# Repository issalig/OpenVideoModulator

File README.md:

# rgbs
rgbs is an Open Hardware adapter that converts an RGB video signal to Composite and S-Video.

This is a fork of https://github.com/SukkoPera/OpenVideoModulator with independent RCA and SVideo connector, pin header for output signals and 5V DC jack.

There are also designs for breakout boards that could be inside CPC 464 and 6128 and it would be plugged on the space left in the left side (viewed from rear) of the expansion port. 
It requires to open the computer and solder wires from RGBS 5V GND to the breakout board, then it could be connected with right angle pinheaders to the main board saving the additional 5V line.

I have NOT physically checked this. So, trying is up to you.

## Summary
This project is an Open Hardware implementation of [a small circuit found on the Amstrad CPC Wiki](http://www.cpcwiki.eu/index.php/RGB_SVideo) that is able to produce a composite video signal from separate red, green and blue color component signals (plus sync). Since it uses the AD724 encoder, it is also able to produce an S-Video (Y/C) signal and it supports both the PAL and NTSC standards.

## Assembly and Usage

The crystal frequency depends on your choice: use 4.433619 MHz for PAL or 3.579545 MHz for NTSC.

Solder the AD724 chip first, then all surface-mount components. Finally complete the board with the through-hole connectors and crystal.

One of C6 and C7 should be enough. I use a 100uF on C6 but that is probably overkill. Play with them if your output video signal is unstable.

Usage should be straightforward: just provide power (make sure to match the polarity!) and video signals to the board, then get your output from the other side. Note that the *sync* input requires a *composite sync* signal.

## Problems and troubleshooting

If you get BW image check AD724 soldering.

In case of noise, check or change capacitors.

## Known issues

Quality is not the best. On my CPC I get black areas on the right side of characters.
If you know how to solve just tell it and we will improve the design.

## License
 Do whatever you want with it but give me credit.
 
## Thanks
- CPC Wiki for the original circuit.
- SukkoPera for original board

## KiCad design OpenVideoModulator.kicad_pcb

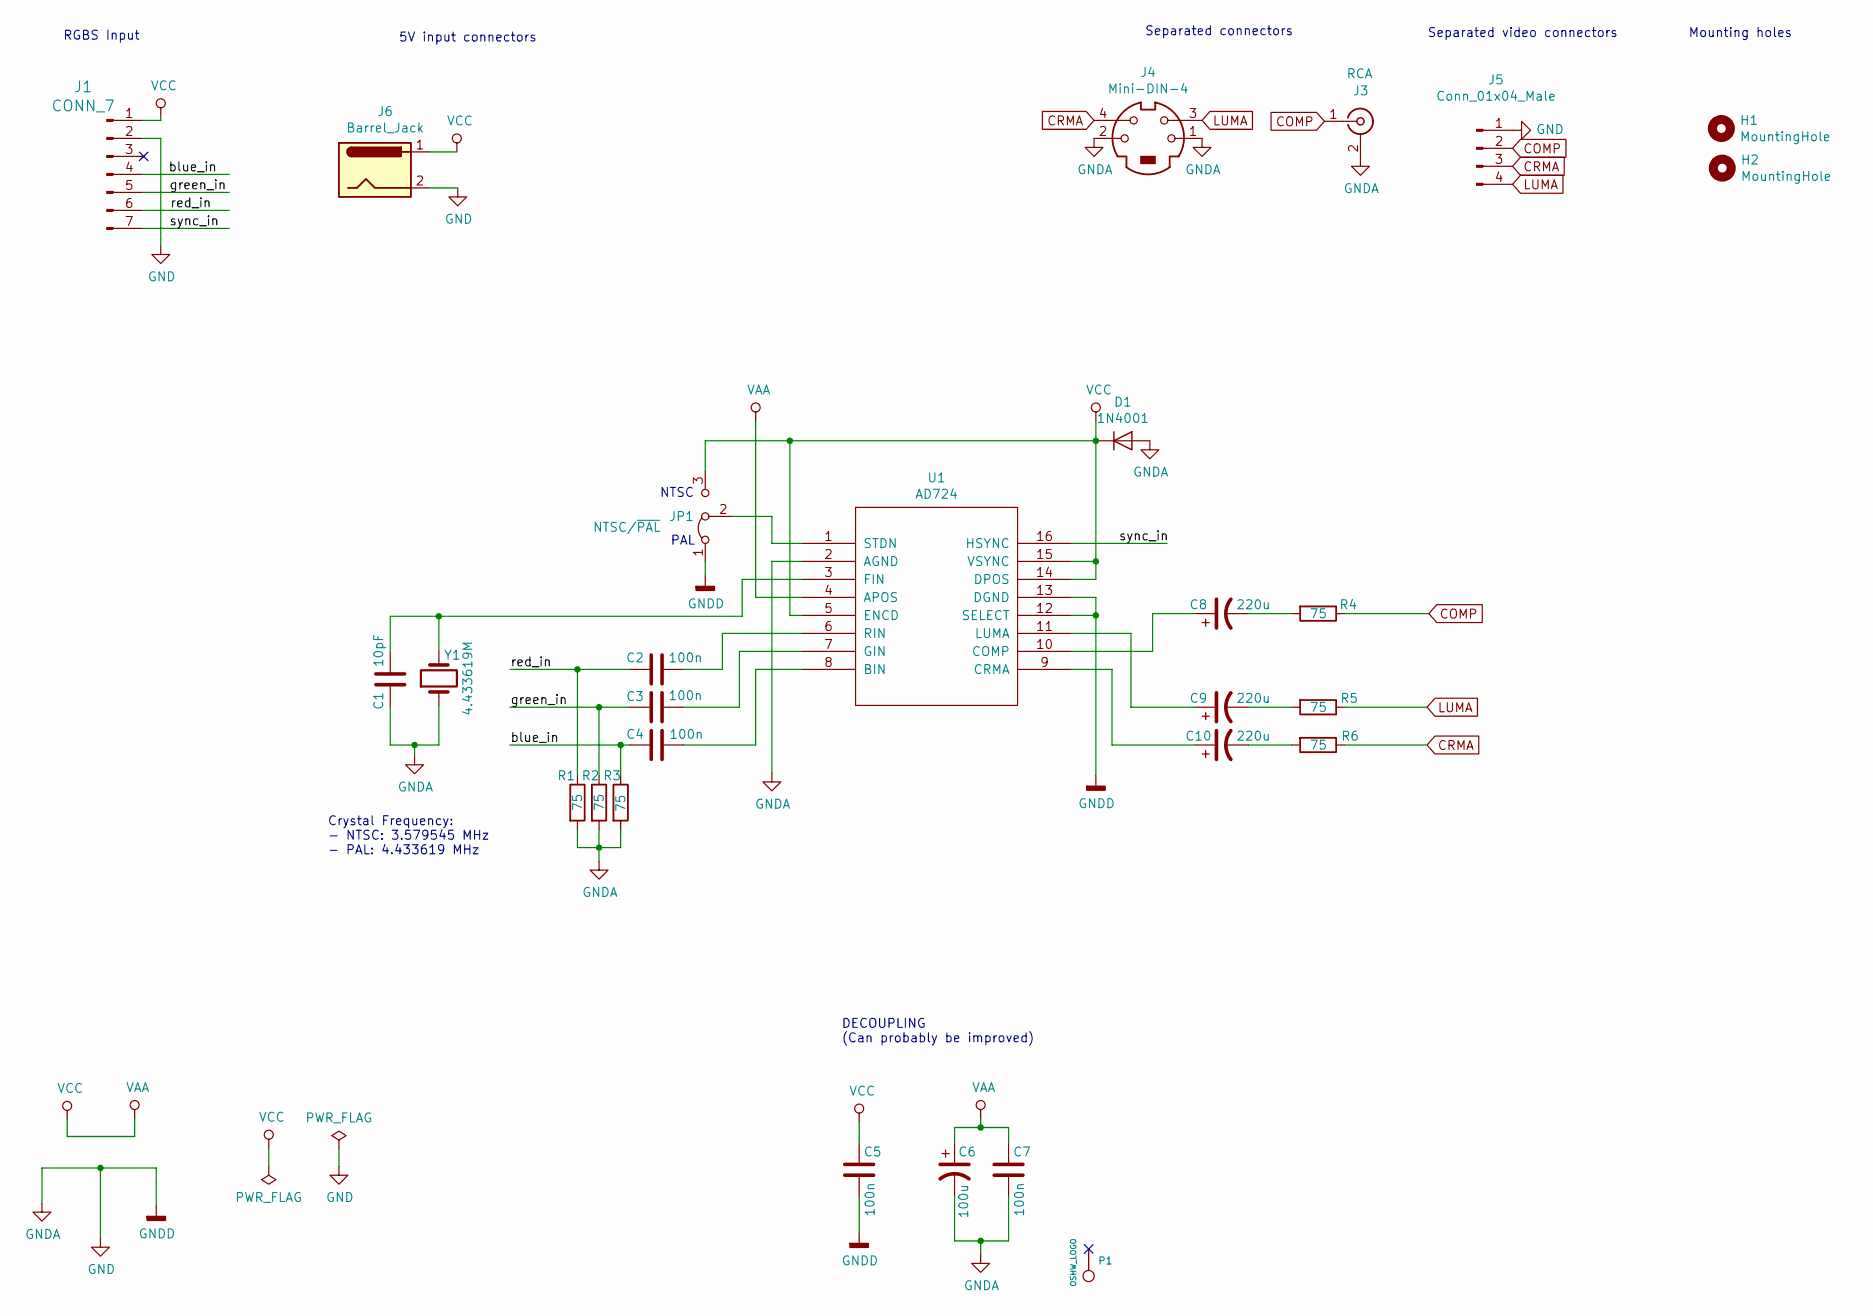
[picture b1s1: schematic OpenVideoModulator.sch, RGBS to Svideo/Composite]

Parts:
C1: 10pF; C_0805_2012Metric_Pad1.15x1.40mm_HandSolder
C2, C3, C4, C5, C7: 100n; C_0805_2012Metric_Pad1.15x1.40mm_HandSolder
C6: 100u; CP_Radial_D5.0mm_P2.00mm
C8, C9, C10: 220u; CP_Radial_D5.0mm_P2.00mm
D1: 1N4001; D_SMA
H1, H2: MountingHole; MountingHole_2.2mm_M2_ISO7380_Pad
J1: CONN_7; PinHeader_1x07_P2.54mm_Vertical
J3: RCA; CUI_RCJ-044
J4: Mini-DIN-4; CUI_MD-40S_1234
J5: Conn_01x04_Male; PinHeader_1x04_P2.54mm_Vertical
J6: Barrel_Jack; BarrelJack_Horizontal
JP1: NTSC/~PAL; PinHeader_1x03_P2.54mm_Vertical
P1: OSHW_LOGO; OSHW-Logo2_7.3x6mm_Copper
R1, R2, R3, R4, R5, R6: 75; R_0805_2012Metric_Pad1.15x1.40mm_HandSolder
U1: AD724; SOIC-16W_7.5x10.3mm_P1.27mm
Y1: 4.433619M; Crystal_HC49-4H_Vertical

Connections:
/blue_in: C4.2, J1.4, R3.1
/green_in: C3.2, J1.5, R2.1
/red_in: C2.2, J1.6, R1.1
/sync_in: J1.7, U1.16 (HSYNC)
COMP: J3.1 (In), J5.2, R4.1
CRMA: J4.4, J5.3, R6.1
GND: C1.2, C5.1, C6.2, C7.1, D1.2 (A), J1.2, J3.2 (Ext), J4.1, J4.2, J5.1, J6.2, JP1.1 (A), R1.2, R2.2, R3.2, U1.2 (AGND), U1.12 (SELECT), U1.13 (DGND), Y1.1
LUMA: J4.3, J5.4, R5.1
unnamed: C1.1, U1.3 (FIN), Y1.2
unnamed: C2.1, U1.6 (RIN)
unnamed: C3.1, U1.7 (GIN)
unnamed: C4.1, U1.8 (BIN)
unnamed: C8.1, U1.10 (COMP)
unnamed: C8.2, R4.2
unnamed: C9.1, U1.11 (LUMA)
unnamed: C9.2, R5.2
unnamed: C10.1, U1.9 (CRMA)
unnamed: C10.2, R6.2
unnamed: JP1.2 (C), U1.1 (STDN)
VAA: C5.2, C6.1, C7.2, D1.1 (K), J1.1, J6.1, JP1.3 (B), U1.4 (APOS), U1.5 (ENCD), U1.14 (DPOS), U1.15 (VSYNC)

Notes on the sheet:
PAL
NTSC
Crystal Frequency: - NTSC: 3.579545 MHz - PAL: 4.433619 MHz
Separated connectors
DECOUPLING (Can probably be improved)
RGBS Input
5V input connectors
Mounting holes
Separated video connectors

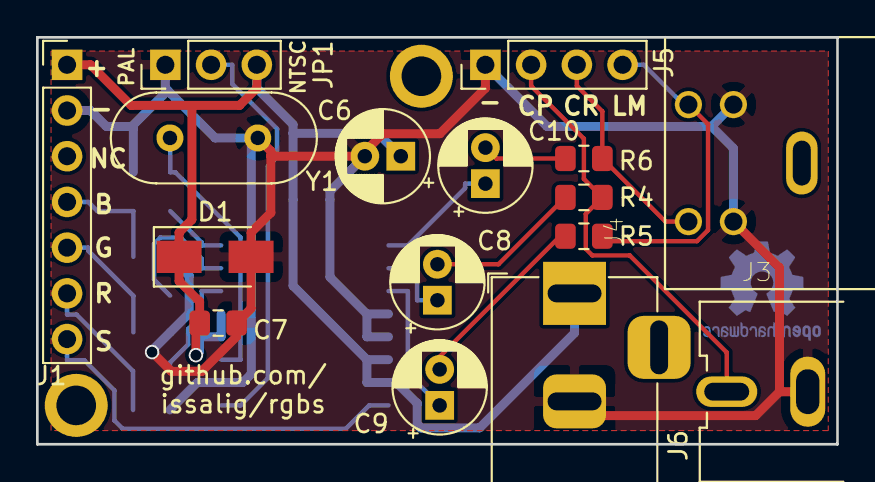
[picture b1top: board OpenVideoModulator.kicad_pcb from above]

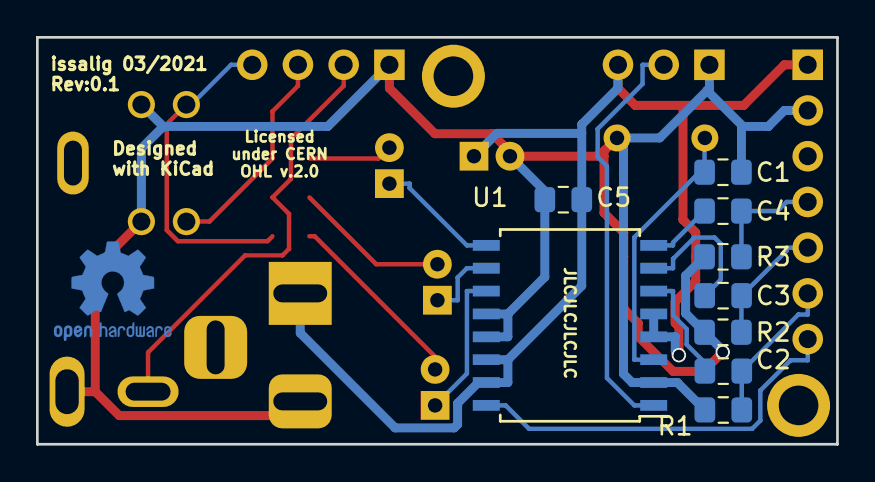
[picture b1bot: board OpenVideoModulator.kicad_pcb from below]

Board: 2 copper layers, 44.5 x 22.6 mm, 28 parts (10 on the bottom side), 20 nets.

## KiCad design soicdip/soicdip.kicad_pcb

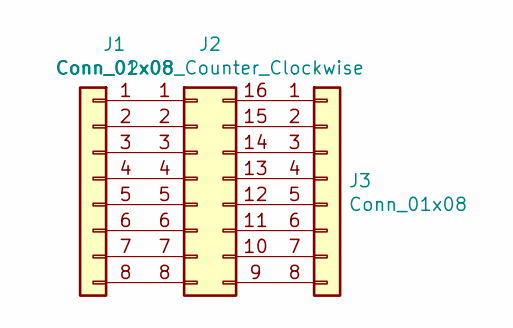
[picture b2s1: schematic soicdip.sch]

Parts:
J1, J3: Conn_01x08; PinHeader_1x08_P2.54mm_Vertical
J2: Conn_02x08_Counter_Clockwise; SOIC-16

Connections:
unnamed: J1.1, J2.1
unnamed: J1.2, J2.2
unnamed: J1.3, J2.3
unnamed: J1.4, J2.4
unnamed: J1.5, J2.5
unnamed: J1.6, J2.6
unnamed: J1.7, J2.7
unnamed: J1.8, J2.8
unnamed: J2.9, J3.8
unnamed: J2.10, J3.7
unnamed: J2.11, J3.6
unnamed: J2.12, J3.5
unnamed: J2.13, J3.4
unnamed: J2.14, J3.3
unnamed: J2.15, J3.2
unnamed: J2.16, J3.1

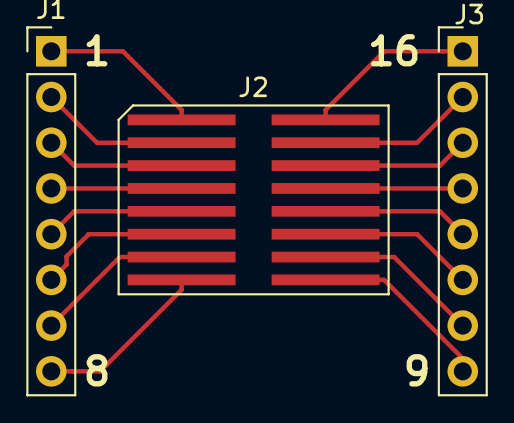
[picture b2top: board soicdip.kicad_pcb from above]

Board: 2 copper layers, 3 parts (0 on the bottom side), 16 nets.

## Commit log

2021-03-07 1st version
2021-03-07 readme
2021-03-07 6128 pcb
2021-03-09 panelizing experiments
2021-03-12 release candidate
2021-03-12 clean
2021-03-12 imgs clean
2021-03-12 internal img
2021-03-12 rgbs
2021-03-12 panelize

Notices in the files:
OpenVideoModulator.kicad_pcb:
Licensed under CERN OHL v.1.2
